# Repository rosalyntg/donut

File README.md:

# Donut

A simple ring light designed for a StereoZoom 4 microscope.

## Basic description

A ring light with adjustable brightness (potentiometer knob) driven by a MP3383 LED driver. It has 60 LEDs on them arranged in a circular pattern to give good lighting.

## Images

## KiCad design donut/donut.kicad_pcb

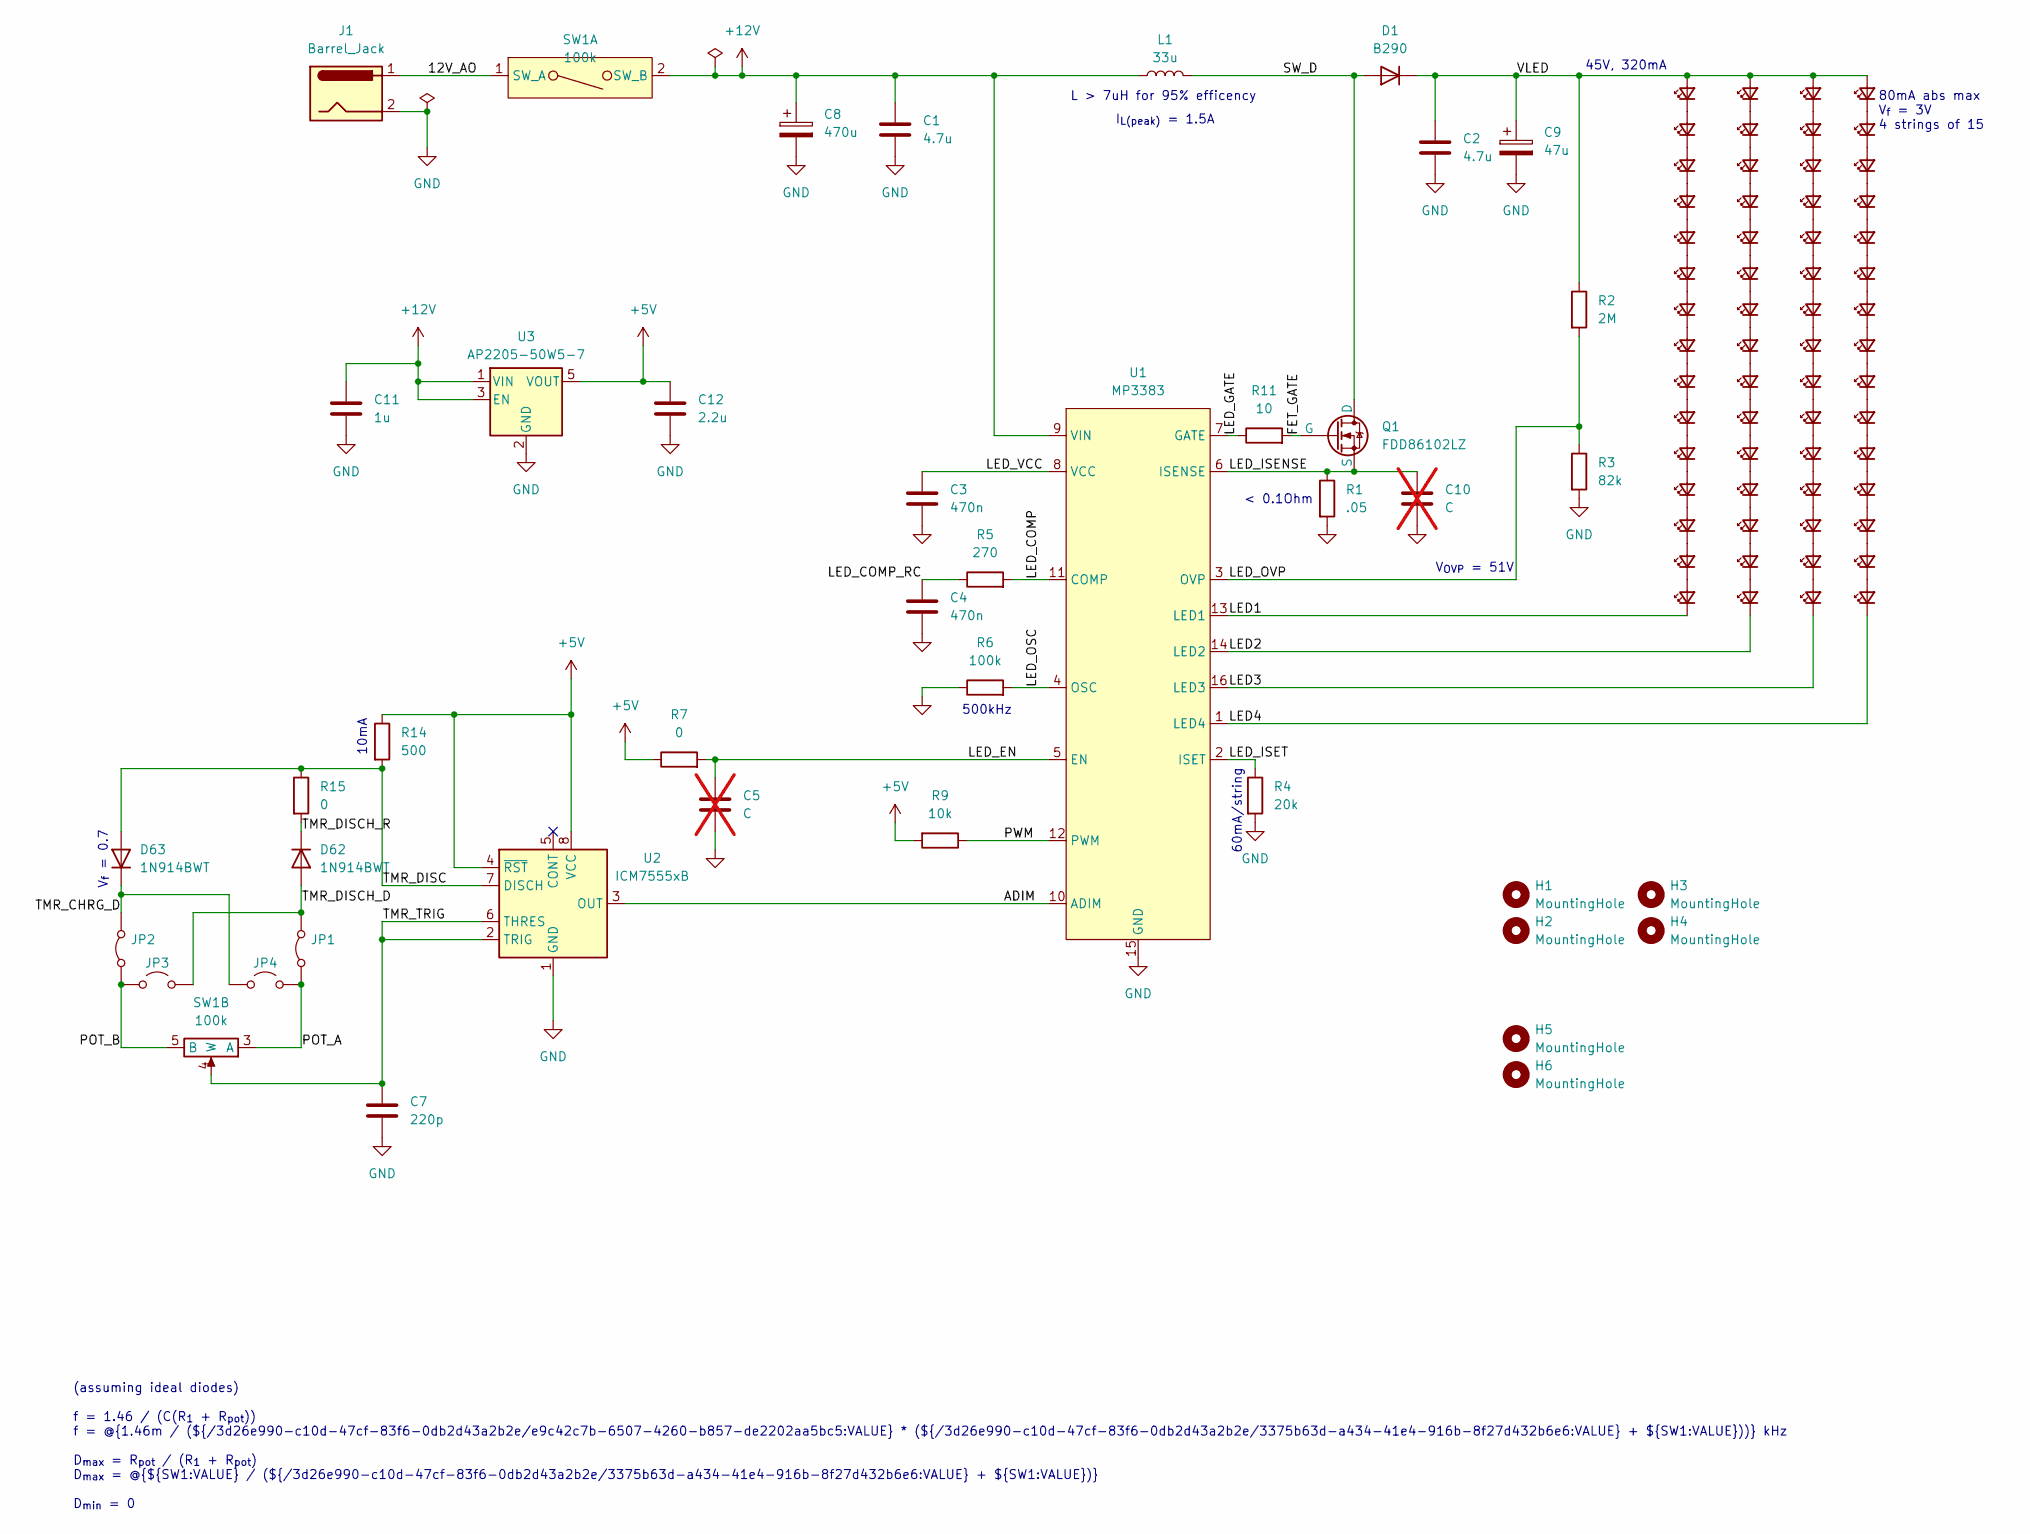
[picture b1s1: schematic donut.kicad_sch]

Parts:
C1, C2: 4.7u; C_0805_2012Metric_Pad1.18x1.45mm_HandSolder; Manufacturer Part Number GRT21BR61H475KE13L; Digikey Part Number 490-12394-1-ND
C3, C4: 470n; C_0805_2012Metric_Pad1.18x1.45mm_HandSolder
C5, C10: C; C_0805_2012Metric_Pad1.18x1.45mm_HandSolder; not fitted
C7: 220p; C_0805_2012Metric_Pad1.18x1.45mm_HandSolder
C8: 470u; CP_Radial_D8.0mm_P3.50mm; Manufacturer Part Number 860020374012; Digikey Part Number 732-8799-1-ND
C9: 47u; CP_Radial_D6.3mm_P2.50mm; Manufacturer Part Number 860020773013; Digikey Part Number 732-8974-1-ND
C11: 1u; C_0805_2012Metric_Pad1.18x1.45mm_HandSolder; Manufacturer Part Number GRM21BR71A10KA01L
C12: 2.2u; C_0805_2012Metric_Pad1.18x1.45mm_HandSolder; Manufacturer Part Number GRM21BR71E225KE11K
D1: B290; D_SMA-SMB_Universal_Handsoldering; Manufacturer Part Number B290-13-F; Digikey Part Number B290-FDICT-ND
D2, D3, D4, D5, D6, D7, D8, D9, D10, D11, D12, D13, D14, D15, D16, D17, D18, D19, D20, D21, D22, D23, D24, D25, D26, D27, D28, D29, D30, D31, D32, D33, D34, D35, D36, D37, D38, D39, D40, D41, D42, D43, D44, D45, D46, D47, D48, D49, D50, D51, D52, D53, D54, D55, D56, D57, D58, D59, D60, D61: LED_Small; IN-P36ATEUW; Manufacturer Part Number IN-P36BTEUW.50; Digikey Part Number IN-P36BTEUW.50
D62, D63: 1N914BWT; D_SOD-523; Manufacturer Part Number 1N914BWT; Digikey Part Number 1N914BWTCT-ND
H1, H2, H3, H4, H5, H6: MountingHole; MountingHole_3.2mm_M3
J1: Barrel_Jack; BarrelJack_CUI_PJ-063AH_Horizontal; Manufacturer Part Number PJ-063AH; Digikey Part Number CP-063AH-ND
JP1, JP2: Jumper_2_Bridged; SolderJumper-2_P1.3mm_Bridged_RoundedPad1.0x1.5mm
JP3, JP4: Jumper_2_Open; SolderJumper-2_P1.3mm_Open_RoundedPad1.0x1.5mm
L1: 33u; L_APV_APH0840; Manufacturer Part Number PA5449.333NLT; Digikey Part Number 553-PA5449.333NLTCT-ND
Q1: FDD86102LZ; TO-252-2_TabPin1; Manufacturer Part Number FDD86102LZ; Digikey Part Number FDD86102LZFSCT-ND
R1: .05; R_0805_2012Metric_Pad1.20x1.40mm_HandSolder; Manufacturer Part Number RL1220T-R050-G; Digikey Part Number RL12T.05GCT-ND
R2: 2M; R_0805_2012Metric_Pad1.20x1.40mm_HandSolder
R3: 82k; R_0805_2012Metric_Pad1.20x1.40mm_HandSolder
R4: 20k; R_0805_2012Metric_Pad1.20x1.40mm_HandSolder
R5: 270; R_0805_2012Metric_Pad1.20x1.40mm_HandSolder
R6: 100k; R_0805_2012Metric_Pad1.20x1.40mm_HandSolder
R7, R15: 0; R_0805_2012Metric_Pad1.20x1.40mm_HandSolder
R9: 10k; R_0805_2012Metric_Pad1.20x1.40mm_HandSolder
R11: 10; R_0805_2012Metric_Pad1.20x1.40mm_HandSolder
R14: 500; R_0805_2012Metric_Pad1.20x1.40mm_HandSolder
SW1: 100k; Potentiometer_P091S; Manufacturer Part Number P091S-FC20BR10K; Digikey Part Number 987-1283-ND
U1: MP3383; SOIC-16_3.9x9.9mm_P1.27mm; Manufacturer Part Number MP3383GS-P; Digikey Part Number 1589-MP3383GS-PCT-ND
U2: ICM7555xB; SOIC-8_3.9x4.9mm_P1.27mm; Manufacturer Part Number ICM7555CBAZ-T; Digikey Part Number ICM7555CBAZ-TCT-ND
U3: AP2205-50W5-7; SOT-23-5; Manufacturer Part Number AP2205-50W5-7; Digikey Part Number 31-AP2205-50W5-7CT-ND

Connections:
+5V: C12.1, R7.1, R9.2, R14.1, U2.4 (~RST), U2.8 (VCC), U3.5 (VOUT)
+12V: C1.1, C8.1, C11.1, L1.1, SW1.2 (SW_B), U1.9 (VIN), U3.1 (VIN), U3.3 (EN)
/12V_AO: J1.1, SW1.1 (SW_A)
/ADIM: U1.10 (ADIM), U2.3 (OUT)
/FET_GATE: Q1.2 (G), R11.2
/LED1: D46.1 (K), U1.13 (LED1)
/LED2: D31.1 (K), U1.14 (LED2)
/LED3: D2.1 (K), U1.16 (LED3)
/LED4: D61.1 (K), U1.1 (LED4)
/LED_COMP: R5.2, U1.11 (COMP)
/LED_COMP_RC: C4.1, R5.1
/LED_EN: C5.1, R7.2, U1.5 (EN)
/LED_GATE: R11.1, U1.7 (GATE)
/LED_ISENSE: C10.1, Q1.3 (S), R1.1, U1.6 (ISENSE)
/LED_ISET: R4.1, U1.2 (ISET)
/LED_OSC: R6.2, U1.4 (OSC)
/LED_OVP: R2.2, R3.1, U1.3 (OVP)
/LED_VCC: C3.1, U1.8 (VCC)
/POT_A: JP1.1 (A), JP4.2 (B), SW1.3 (A)
/POT_B: JP2.1 (A), JP3.1 (A), SW1.5 (B)
/PWM: R9.1, U1.12 (PWM)
/SW_D: D1.2 (A), L1.2, Q1.1 (D)
/TMR_CHRG_D: D63.1 (K), JP2.2 (B), JP4.1 (A)
/TMR_DISC: D63.2 (A), R14.2, R15.1, U2.7 (DISCH)
/TMR_DISCH_D: D62.2 (A), JP1.2 (B), JP3.2 (B)
/TMR_DISCH_R: D62.1 (K), R15.2
/TMR_TRIG: C7.1, SW1.4 (W), U2.2 (TRIG), U2.6 (THRES)
/VLED: C2.1, C9.1, D1.1 (K), D16.2 (A), D17.2 (A), D32.2 (A), D47.2 (A), R2.1
GND: C1.2, C2.2, C3.2, C4.2, C5.2, C7.2, C8.2, C9.2, C10.2, C11.2, C12.2, J1.2, R1.2, R3.2, R4.2, R6.1, U1.15 (GND), U2.1 (GND), U3.2 (GND)
unnamed: D2.2 (A), D3.1 (K)
unnamed: D3.2 (A), D4.1 (K)
unnamed: D4.2 (A), D5.1 (K)
unnamed: D5.2 (A), D6.1 (K)
unnamed: D6.2 (A), D7.1 (K)
unnamed: D7.2 (A), D8.1 (K)
unnamed: D8.2 (A), D9.1 (K)
unnamed: D10.2 (A), D11.1 (K)
unnamed: D9.2 (A), D10.1 (K)
unnamed: D11.2 (A), D12.1 (K)
unnamed: D12.2 (A), D13.1 (K)
unnamed: D13.2 (A), D14.1 (K)
unnamed: D14.2 (A), D15.1 (K)
unnamed: D15.2 (A), D16.1 (K)
unnamed: D17.1 (K), D18.2 (A)
unnamed: D18.1 (K), D19.2 (A)
unnamed: D19.1 (K), D20.2 (A)
unnamed: D20.1 (K), D21.2 (A)
unnamed: D21.1 (K), D22.2 (A)
unnamed: D22.1 (K), D23.2 (A)
unnamed: D23.1 (K), D24.2 (A)
unnamed: D24.1 (K), D25.2 (A)
unnamed: D25.1 (K), D26.2 (A)
unnamed: D26.1 (K), D27.2 (A)
unnamed: D27.1 (K), D28.2 (A)
unnamed: D28.1 (K), D29.2 (A)
unnamed: D29.1 (K), D30.2 (A)
unnamed: D30.1 (K), D31.2 (A)
unnamed: D32.1 (K), D33.2 (A)
unnamed: D33.1 (K), D34.2 (A)
unnamed: D34.1 (K), D35.2 (A)
unnamed: D35.1 (K), D36.2 (A)
unnamed: D36.1 (K), D37.2 (A)
unnamed: D37.1 (K), D38.2 (A)
unnamed: D38.1 (K), D39.2 (A)
unnamed: D39.1 (K), D40.2 (A)
unnamed: D40.1 (K), D41.2 (A)
unnamed: D41.1 (K), D42.2 (A)
unnamed: D42.1 (K), D43.2 (A)
unnamed: D43.1 (K), D44.2 (A)
unnamed: D44.1 (K), D45.2 (A)
unnamed: D45.1 (K), D46.2 (A)
unnamed: D47.1 (K), D48.2 (A)
unnamed: D48.1 (K), D49.2 (A)
unnamed: D49.1 (K), D50.2 (A)
unnamed: D50.1 (K), D51.2 (A)
unnamed: D51.1 (K), D52.2 (A)
unnamed: D52.1 (K), D53.2 (A)
unnamed: D53.1 (K), D54.2 (A)
unnamed: D54.1 (K), D55.2 (A)
unnamed: D55.1 (K), D56.2 (A)
unnamed: D56.1 (K), D57.2 (A)
unnamed: D57.1 (K), D58.2 (A)
unnamed: D58.1 (K), D59.2 (A)
unnamed: D59.1 (K), D60.2 (A)
unnamed: D60.1 (K), D61.2 (A)

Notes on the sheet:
V_{OVP} = 51V
45V, 320mA
I_{L(peak)} = 1.5A
< 0.1Ohm
(assuming ideal diodes) f = 1.46 / (C(R_{1} + R_{pot})) f = @{1.46m / (${/3d26e990-c10d-47cf-83f6-0db2d43a2b2e/e9c42c7b-6507-4260-b857-de2202aa5bc5:VALUE} * (${/3d26e990-c10d-47cf-83f6-0db2d43a2b2e/3375b63d-a434-41e4-916b-8f27d432b6e6:VALUE} + ${SW1:VALUE}))} kHz D_{max} = R_{pot} / (R_{1} + R_{pot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
L > 7uH for 95% efficency
V_{f} = 0.7
80mA abs max V_{f} = 3V 4 strings of 15
10mA
60mA/string
500kHz

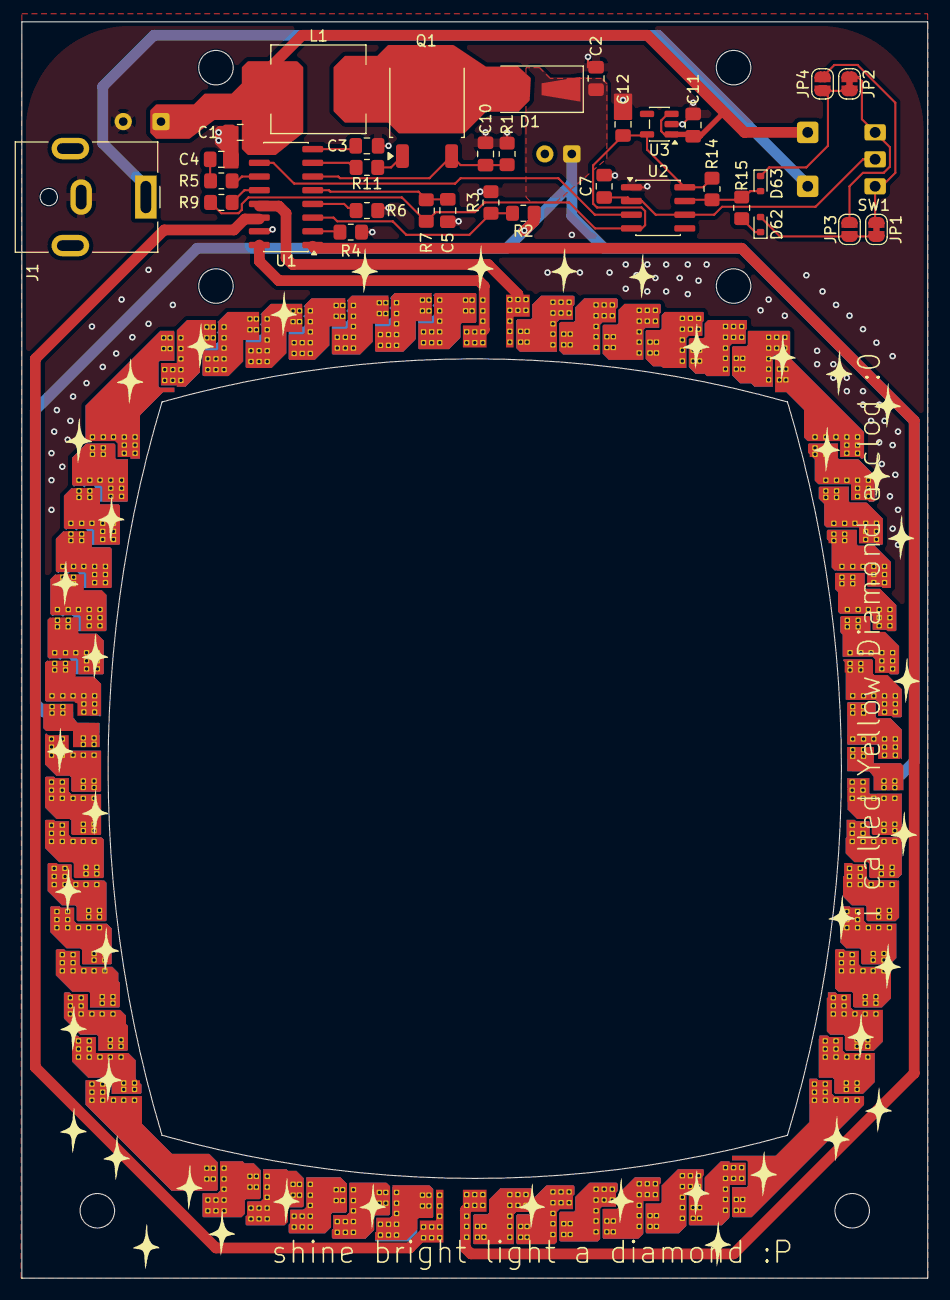
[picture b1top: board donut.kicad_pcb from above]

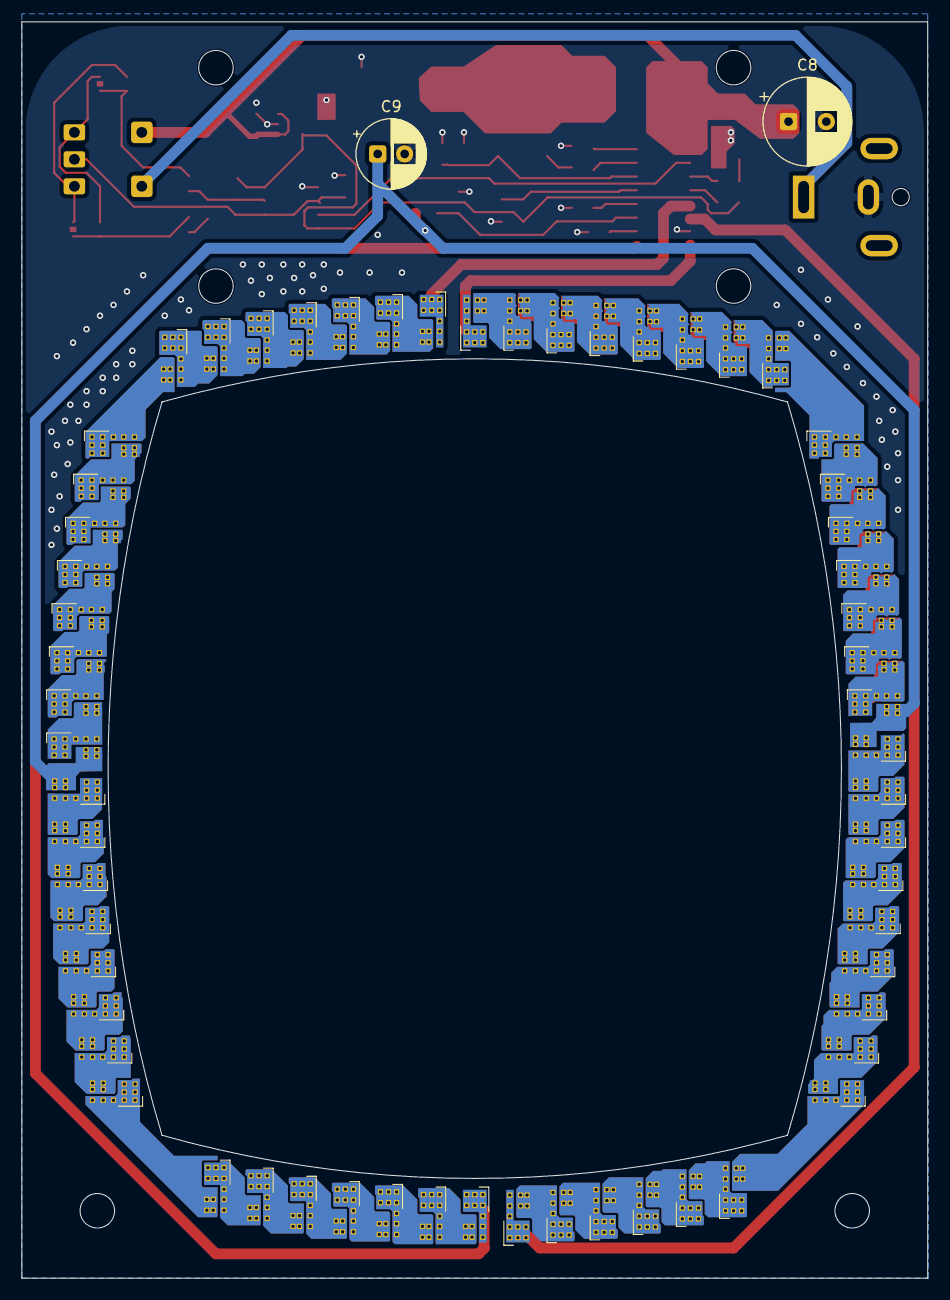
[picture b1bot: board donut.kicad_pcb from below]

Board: 2 copper layers, 84.0 x 116.5 mm, 102 parts (62 on the bottom side), 85 nets.
